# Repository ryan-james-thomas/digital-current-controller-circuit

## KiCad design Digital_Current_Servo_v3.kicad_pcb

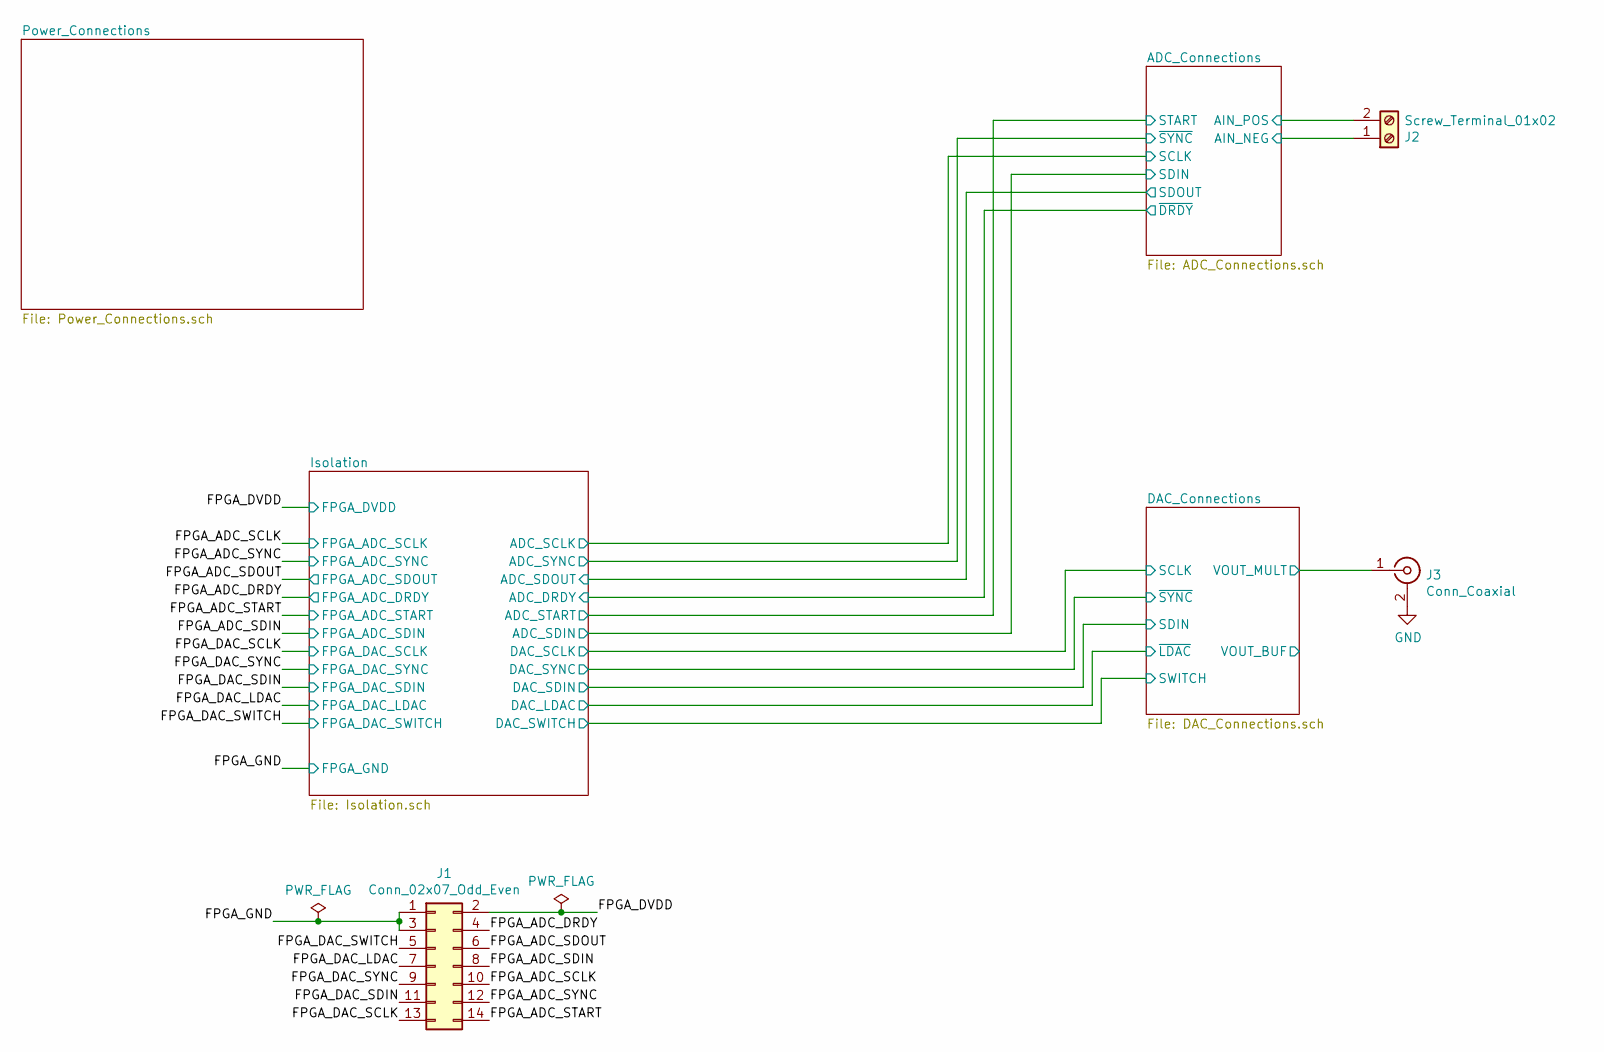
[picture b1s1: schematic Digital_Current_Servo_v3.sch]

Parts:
J1: Conn_02x07_Odd_Even; PinHeader_2x07_P2.54mm_Vertical; Digikey Part Number S2012EC-07-ND
J2: Screw_Terminal_01x02; TerminalBlock_bornier-2_P5.08mm; Digikey Part Number 732-10955-ND
J3: Conn_Coaxial; BNC_Amphenol_B6252HB-NPP3G-50_Horizontal; Digikey Part Number WM5514-ND

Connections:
/ADC_Connections/AIN_NEG: J2.1; also elsewhere on the board
/ADC_Connections/AIN_POS: J2.2; also elsewhere on the board
/DAC_Connections/VOUT_MULT: J3.1 (In); also elsewhere on the board
/FPGA_ADC_DRDY: J1.4; also elsewhere on the board
/FPGA_ADC_SCLK: J1.10; also elsewhere on the board
/FPGA_ADC_SDIN: J1.8; also elsewhere on the board
/FPGA_ADC_SDOUT: J1.6; also elsewhere on the board
/FPGA_ADC_START: J1.14; also elsewhere on the board
/FPGA_ADC_SYNC: J1.12; also elsewhere on the board
/FPGA_DAC_LDAC: J1.7; also elsewhere on the board
/FPGA_DAC_SCLK: J1.13; also elsewhere on the board
/FPGA_DAC_SDIN: J1.11; also elsewhere on the board
/FPGA_DAC_SWITCH: J1.5; also elsewhere on the board
/FPGA_DAC_SYNC: J1.9; also elsewhere on the board
/FPGA_DVDD: J1.2; also elsewhere on the board
/FPGA_GND: J1.1, J1.3; also elsewhere on the board
GND: J3.2 (Ext); also elsewhere on the board

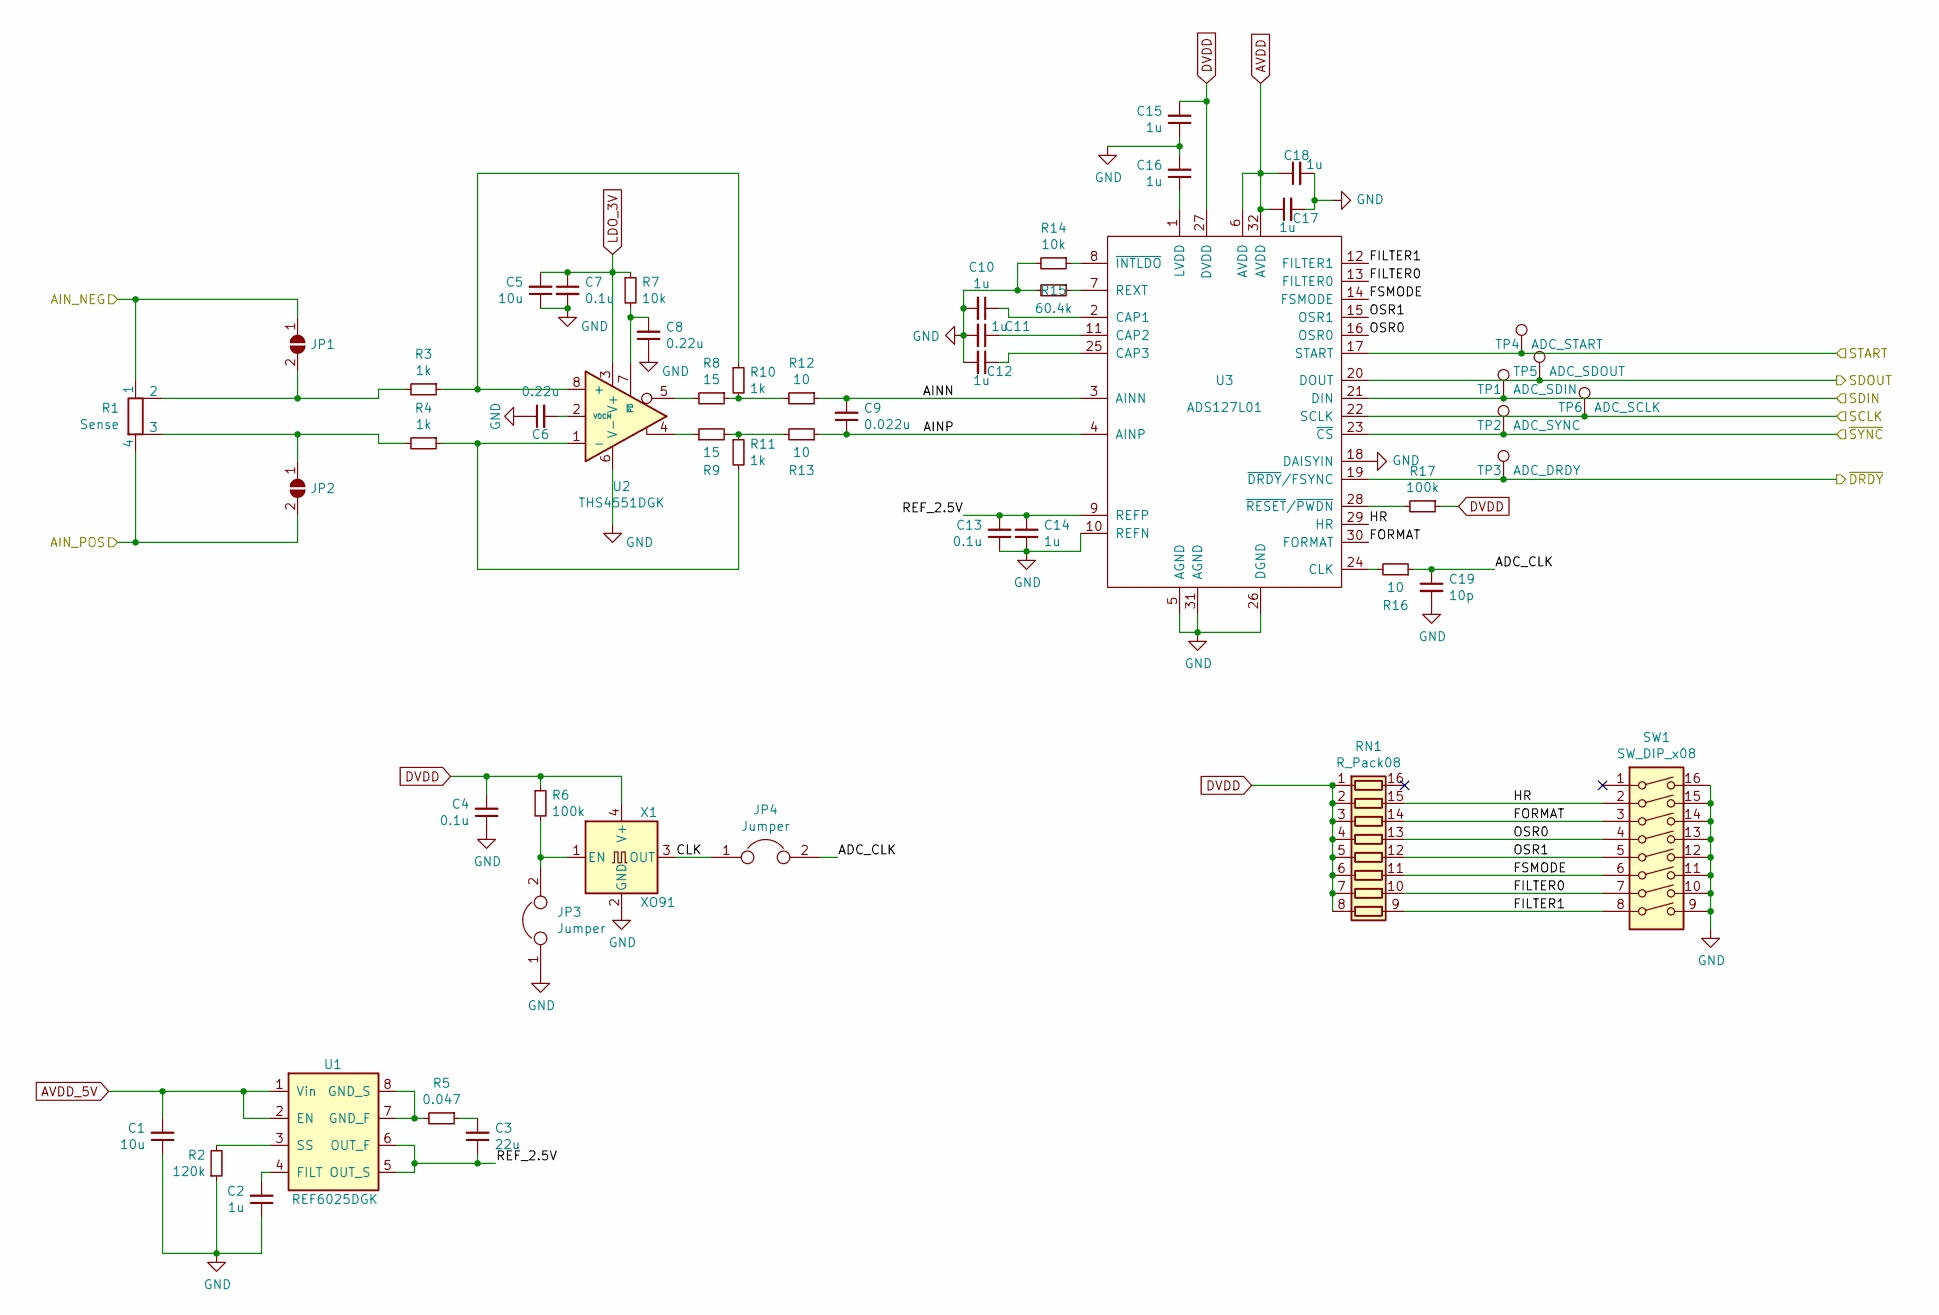
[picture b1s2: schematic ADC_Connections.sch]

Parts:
C1, C5: 10u; C_0805_2012Metric_Pad1.15x1.40mm_HandSolder; Digikey Part Number 1276-1052-1-ND
C2, C10, C11, C12, C14, C15, C16, C17, C18: 1u; C_0805_2012Metric_Pad1.15x1.40mm_HandSolder; Digikey Part Number 1276-6471-1-ND
C3: 22u; C_1206_3216Metric_Pad1.42x1.75mm_HandSolder; Digikey Part Number 1276-1771-1-ND
C4, C7, C13: 0.1u; C_0805_2012Metric_Pad1.15x1.40mm_HandSolder; Digikey Part Number 1276-1003-1-ND
C6, C8: 0.22u; C_0805_2012Metric_Pad1.15x1.40mm_HandSolder; Digikey Part Number 1276-6478-1-ND
C9: 0.022u; C_0805_2012Metric_Pad1.15x1.40mm_HandSolder; Digikey Part Number 399-1163-1-ND
C19: 10p; C_0805_2012Metric_Pad1.15x1.40mm_HandSolder; Digikey Part Number 1276-1109-1-ND
JP1, JP2: SolderJumper_2_Open; SolderJumper-2_P1.3mm_Open_Pad1.0x1.5mm
JP3, JP4: Jumper; PinHeader_1x02_P2.54mm_Vertical; Digikey Part Number S1012EC-02-ND
R1: Sense; TO-220-4_Vertical; Digikey Part Number Y1690-10A-ND
R2: 120k; R_0805_2012Metric_Pad1.15x1.40mm_HandSolder; Digikey Part Number RR12P120KDCT-ND
R3, R4, R10, R11: 1k; R_0805_2012Metric_Pad1.15x1.40mm_HandSolder; Digikey Part Number P1.0KDACT-ND
R5: 0.047; R_0805_2012Metric_Pad1.15x1.40mm_HandSolder; Digikey Part Number 1276-6158-1-ND
R6, R17: 100k; R_0805_2012Metric_Pad1.15x1.40mm_HandSolder; Digikey Part Number 1276-3512-1-ND‎
R7, R14: 10k; R_0805_2012Metric_Pad1.15x1.40mm_HandSolder; Digikey Part Number ‎P10.0KCCT-ND‎
R8, R9: 15; R_0805_2012Metric_Pad1.15x1.40mm_HandSolder; Digikey Part Number YAG4833CT-ND
R12, R13, R16: 10; R_0805_2012Metric_Pad1.15x1.40mm_HandSolder; Digikey Part Number A119971CT-ND
R15: 60.4k; R_0805_2012Metric_Pad1.15x1.40mm_HandSolder; Digikey Part Number RR12P60.4KDCT-ND
RN1: R_Pack08; SOIC-16_W4.9_P1.27; Digikey Part Number 4816P-T01-104LF-ND
SW1: SW_DIP_x08; SOIC-16_W8.6mm_P2.54mm; Digikey Part Number CT2198LPST-ND
TP1: ADC_SDIN; TestPoint_Pad_1.0x1.0mm
TP2: ADC_SYNC; TestPoint_Pad_1.0x1.0mm
TP3: ADC_DRDY; TestPoint_Pad_1.0x1.0mm
TP4: ADC_START; TestPoint_Pad_1.0x1.0mm
TP5: ADC_SDOUT; TestPoint_Pad_1.0x1.0mm
TP6: ADC_SCLK; TestPoint_Pad_1.0x1.0mm
U1: REF6025DGK; VSSOP-8_3.0x3.0mm_P0.65mm; Digikey Part Number 296-51527-1-ND
U2: THS4551DGK; VSSOP-8_3.0x3.0mm_P0.65mm; Digikey Part Number 296-47312-1-ND
U3: ADS127L01; LQFP-32_5x5mm_P0.5mm; Digikey Part Number 296-44344-1-ND
X1: XO91; Oscillator_SMD_Abracon_ASE-4Pin_3.2x2.5mm_HandSoldering; Digikey Part Number 535-11459-1-ND

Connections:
/ADC_Connections/ADC_CLK: C19.1, JP4.2, R16.1
/ADC_Connections/AINN: C9.2, R12.1, U3.3 (AINN)
/ADC_Connections/AINP: C9.1, R13.1, U3.4 (AINP)
/ADC_Connections/AIN_NEG: JP1.1 (A), R1.1; also elsewhere on the board
/ADC_Connections/AIN_POS: JP2.2 (B), R1.4; also elsewhere on the board
/ADC_Connections/CLK: JP4.1, X1.3 (OUT)
/ADC_Connections/FILTER0: RN1.10 (R7.2), SW1.7, U3.13 (FILTER0)
/ADC_Connections/FILTER1: RN1.9 (R8.2), SW1.8, U3.12 (FILTER1)
/ADC_Connections/FORMAT: RN1.14 (R3.2), SW1.3, U3.30 (FORMAT)
/ADC_Connections/FSMODE: RN1.11 (R6.2), SW1.6, U3.14 (FSMODE)
/ADC_Connections/HR: RN1.15 (R2.2), SW1.2, U3.29 (HR)
/ADC_Connections/OSR0: RN1.13 (R4.2), SW1.4, U3.16 (OSR0)
/ADC_Connections/OSR1: RN1.12 (R5.2), SW1.5, U3.15 (OSR1)
/ADC_Connections/REF_2.5V: C3.1, C13.2, C14.2, U1.5 (OUT_S), U1.6 (OUT_F), U3.9 (REFP)
/Isolation/ADC_DRDY: TP3.1, U3.19 (~DRDY~/FSYNC); also elsewhere on the board
/Isolation/ADC_SCLK: TP6.1, U3.22 (SCLK); also elsewhere on the board
/Isolation/ADC_SDIN: TP1.1, U3.21 (DIN); also elsewhere on the board
/Isolation/ADC_SDOUT: TP5.1, U3.20 (DOUT); also elsewhere on the board
/Isolation/ADC_START: TP4.1, U3.17 (START); also elsewhere on the board
/Isolation/ADC_SYNC: TP2.1, U3.23 (~CS); also elsewhere on the board
AVDD: C17.1, C18.1, U3.6 (AVDD), U3.32 (AVDD); also elsewhere on the board
AVDD_5V: C1.2, U1.1 (Vin), U1.2 (EN); also elsewhere on the board
DVDD: C4.2, C15.2, R6.1, R17.1, RN1.1 (R1.1), RN1.2 (R2.1), RN1.3 (R3.1), RN1.4 (R4.1), RN1.5 (R5.1), RN1.6 (R6.1), RN1.7 (R7.1), RN1.8 (R8.1), U3.27 (DVDD), X1.4 (V+); also elsewhere on the board
GND: C1.1, C2.1, C4.1, C5.1, C6.1, C7.2, C8.1, C10.2, C11.2, C12.2, C13.1, C14.1, C15.1, C16.2, C17.2, C18.2, C19.2, JP3.1, R2.1, R14.2, R15.2, SW1.9, SW1.10, SW1.11, SW1.12, SW1.13, SW1.14, SW1.15, SW1.16, U2.6 (V-), U3.5 (AGND), U3.10 (REFN), U3.18 (DAISYIN), U3.26 (DGND), U3.31 (AGND), X1.2 (GND); also elsewhere on the board
LDO_3V: C5.2, C7.1, R7.1, U2.3 (V+); also elsewhere on the board
unnamed: C2.2, U1.4 (FILT)
unnamed: C3.2, R5.1
unnamed: C6.2, U2.2 (VOCM)
unnamed: C8.2, R7.2, U2.7 (~PD)
unnamed: C10.1, U3.2 (CAP1)
unnamed: C11.1, U3.11 (CAP2)
unnamed: C12.1, U3.25 (CAP3)
unnamed: C16.1, U3.1 (LVDD)
unnamed: JP1.2 (B), R1.2, R3.2
unnamed: JP2.1 (A), R1.3, R4.2
unnamed: JP3.2, R6.2, X1.1 (EN)
unnamed: R2.2, U1.3 (SS)
unnamed: R5.2, U1.7 (GND_F), U1.8 (GND_S)
unnamed: R8.2, U2.5
unnamed: R9.1, U2.4
unnamed: R3.1, R10.1, U2.8 (+)
unnamed: R8.1, R10.2, R12.2
unnamed: R9.2, R11.1, R13.2
unnamed: R4.1, R11.2, U2.1 (-)
unnamed: R14.1, U3.8 (~INTLDO)
unnamed: R15.1, U3.7 (REXT)
unnamed: R16.2, U3.24 (CLK)
unnamed: R17.2, U3.28 (~RESET~/~PWDN)

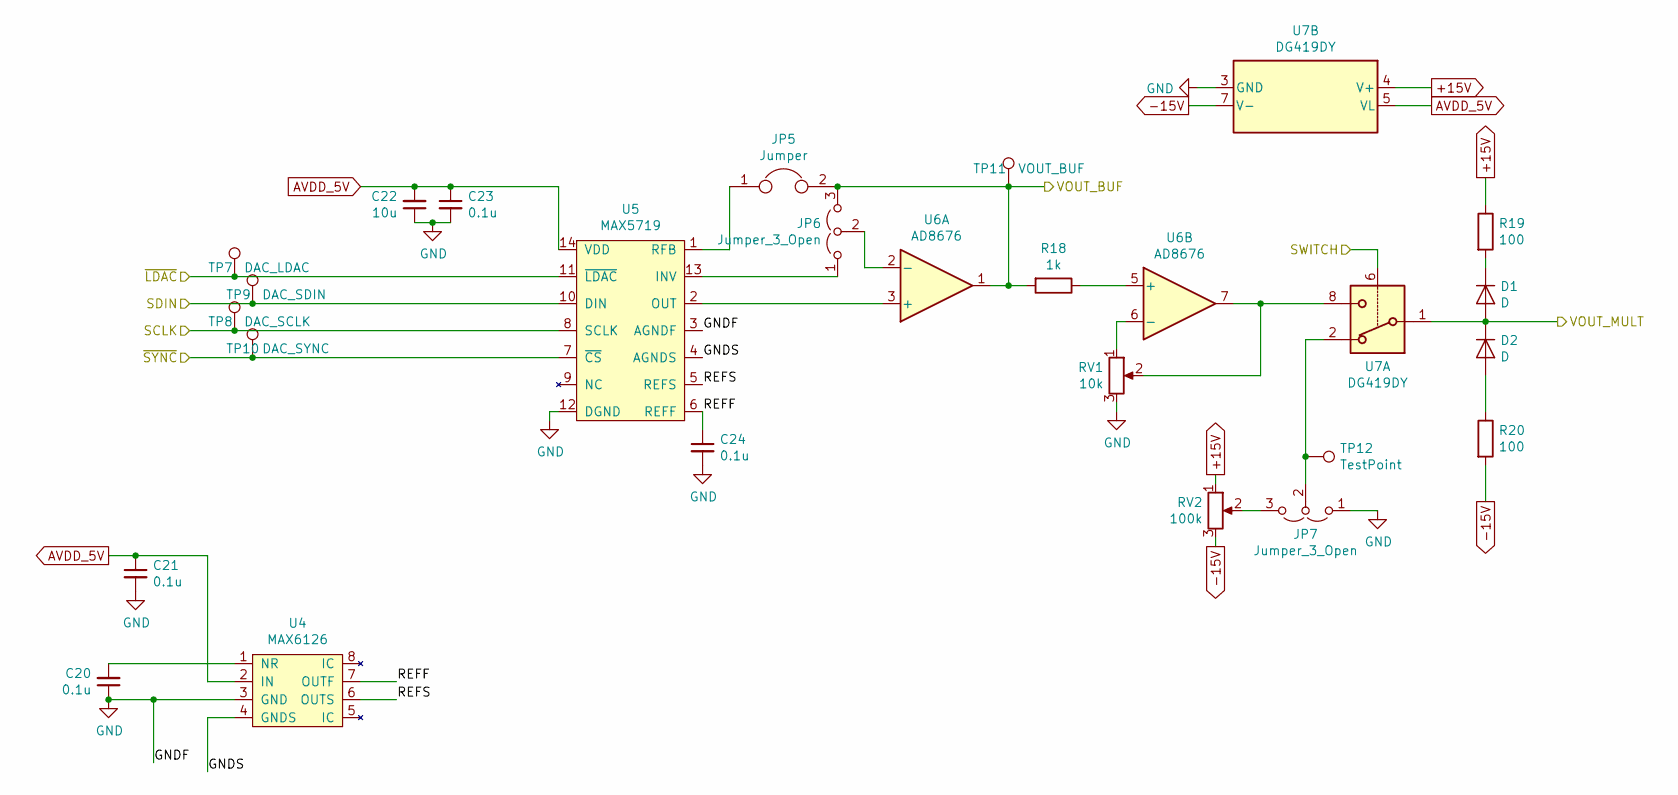
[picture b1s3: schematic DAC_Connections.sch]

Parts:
C20, C21, C23, C24: 0.1u; C_0805_2012Metric_Pad1.15x1.40mm_HandSolder; Digikey Part Number 1276-1003-1-ND
C22: 10u; C_0805_2012Metric_Pad1.15x1.40mm_HandSolder; Digikey Part Number 1276-1052-1-ND
D1, D2: D; D_DO-41_SOD81_P7.62mm_Horizontal; Digikey Part Number 1N4007-TPMSCT-ND
JP5: Jumper; PinHeader_1x02_P2.54mm_Vertical; Digikey Part Number S1012EC-02-ND
JP6, JP7: Jumper_3_Open; PinHeader_1x03_P2.54mm_Vertical; Digikey Part Number S1012EC-03-ND
R18: 1k; R_0805_2012Metric_Pad1.15x1.40mm_HandSolder; Digikey Part Number P1.0KDACT-ND
R19, R20: 100; R_Axial_DIN0207_L6.3mm_D2.5mm_P7.62mm_Horizontal; Digikey Part Number CF14JT100RCT-ND
RV1: 10k; Potentiometer_Bourns_3296W_Vertical; Digikey Part Number 490-2875-ND
RV2: 100k; Potentiometer_Bourns_3296W_Vertical; Digikey Part Number 490-2876-ND
TP7: DAC_LDAC; TestPoint_Pad_1.0x1.0mm
TP8: DAC_SCLK; TestPoint_Pad_1.0x1.0mm
TP9: DAC_SDIN; TestPoint_Pad_1.0x1.0mm
TP10: DAC_SYNC; TestPoint_Pad_1.0x1.0mm
TP11: VOUT_BUF; TestPoint_Pad_1.0x1.0mm
TP12: TestPoint; TestPoint_Pad_1.0x1.0mm
U4: MAX6126; SOIC-8_3.9x4.9mm_P1.27mm; Digikey Part Number MAX6126BASA41+-ND
U5: MAX5719; SOIC-14_3.9x8.7mm_P1.27mm; Digikey Part Number MAX5719GSD+-ND
U6: AD8676; SOIC-8_3.9x4.9mm_P1.27mm; Digikey Part Number AD8676ARZ-ND
U7: DG419DY; SOIC-8_3.9x4.9mm_P1.27mm; Digikey Part Number DG419DY-T1-E3CT-ND

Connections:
+15V: R19.1, RV2.1, U7.4 (V+); also elsewhere on the board
-15V: R20.2, RV2.3, U7.7 (V-); also elsewhere on the board
/DAC_Connections/GNDS: U4.4 (GNDS), U5.4 (AGNDS)
/DAC_Connections/REFF: C24.1, U4.7 (OUTF), U5.6 (REFF)
/DAC_Connections/REFS: U4.6 (OUTS), U5.5 (REFS)
/DAC_Connections/VOUT_BUF: JP5.2, JP6.3 (B), R18.2, TP11.1, U6.1
/DAC_Connections/VOUT_MULT: D1.2 (A), D2.1 (K), U7.1; also elsewhere on the board
/Isolation/DAC_LDAC: TP7.1, U5.11 (~LDAC); also elsewhere on the board
/Isolation/DAC_SCLK: TP8.1, U5.8 (SCLK); also elsewhere on the board
/Isolation/DAC_SDIN: TP9.1, U5.10 (DIN); also elsewhere on the board
/Isolation/DAC_SWITCH: U7.6; also elsewhere on the board
/Isolation/DAC_SYNC: TP10.1, U5.7 (~CS); also elsewhere on the board
AVDD_5V: C21.1, C22.2, C23.1, U4.2 (IN), U5.14 (VDD), U7.5 (VL); also elsewhere on the board
GND: C20.1, C21.2, C22.1, C23.2, C24.2, JP7.1 (A), RV1.3, U4.3 (GND), U5.3 (AGNDF), U5.12 (DGND), U7.3 (GND); also elsewhere on the board
unnamed: C20.2, U4.1 (NR)
unnamed: D1.1 (K), R19.2
unnamed: D2.2 (A), R20.1
unnamed: JP5.1, U5.1 (RFB)
unnamed: JP6.1 (A), U5.13 (INV)
unnamed: JP6.2 (C), U6.2 (-)
unnamed: JP7.2 (C), TP12.1, U7.2
unnamed: JP7.3 (B), RV2.2
unnamed: R18.1, U6.5 (+)
unnamed: RV1.1, U6.6 (-)
unnamed: RV1.2, U6.7, U7.8
unnamed: U5.2 (OUT), U6.3 (+)

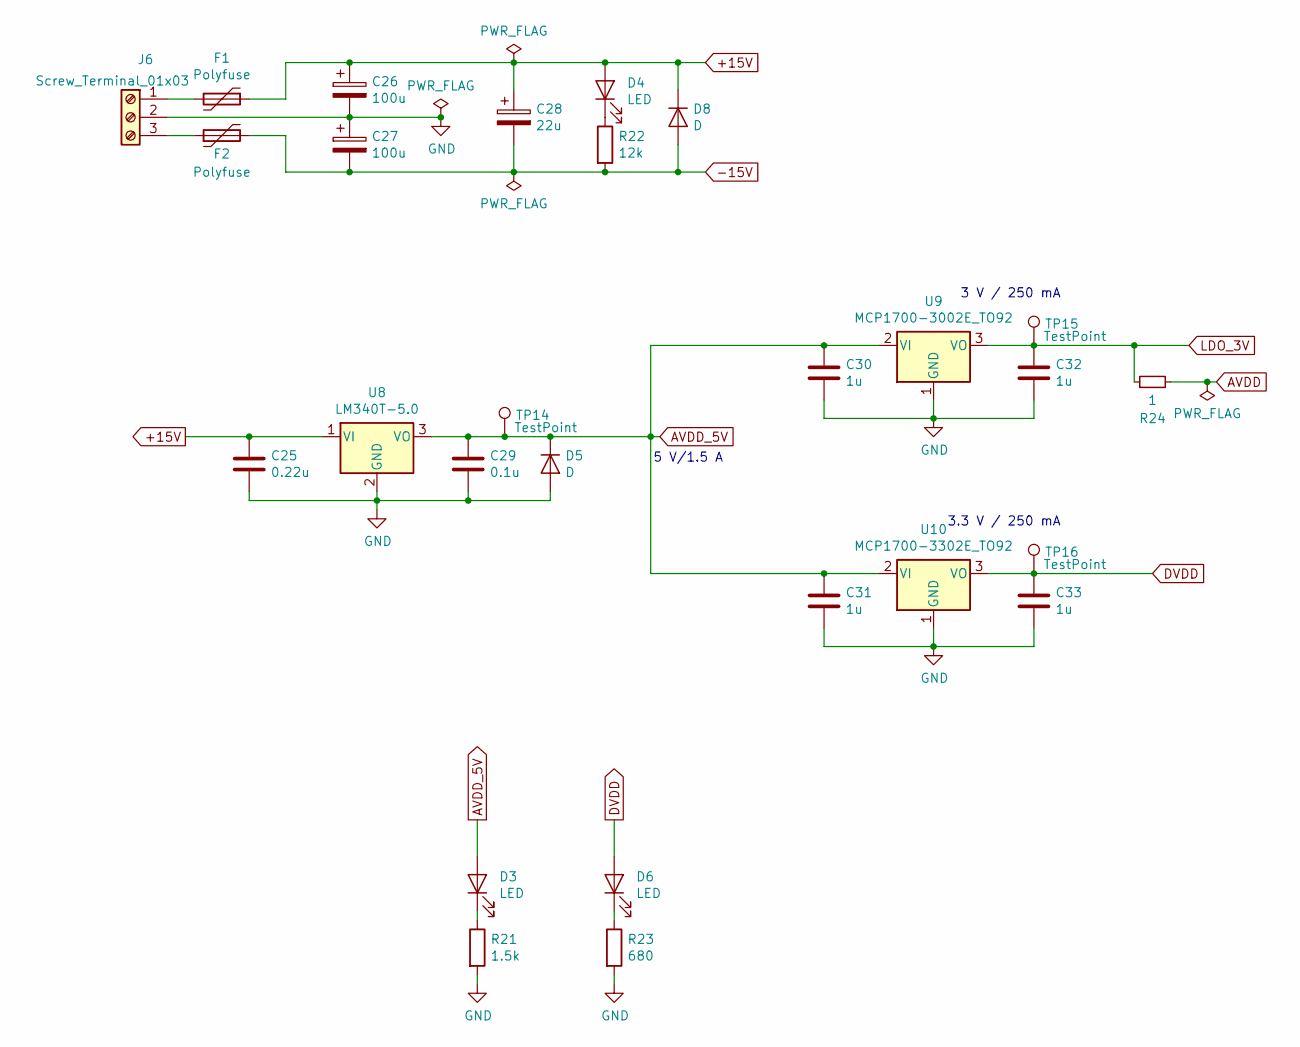
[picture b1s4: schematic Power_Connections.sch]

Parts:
C25: 0.22u; C_0805_2012Metric_Pad1.15x1.40mm_HandSolder; Digikey Part Number 1276-6478-1-ND
C26, C27: 100u; CP_Radial_D8.0mm_P3.50mm; Digikey Part Number 732-8666-1-ND
C28: 22u; CP_Radial_D5.0mm_P2.00mm; Digikey Part Number 732-8662-1-ND
C29: 0.1u; C_0805_2012Metric_Pad1.15x1.40mm_HandSolder; Digikey Part Number 1276-1003-1-ND
C30, C31, C32, C33: 1u; C_0805_2012Metric_Pad1.15x1.40mm_HandSolder; Digikey Part Number 1276-6471-1-ND
D3, D6: LED; LED_0805_2012Metric_Pad1.15x1.40mm_HandSolder; Digikey Part Number 754-2043-1-ND
D4: LED; LED_D5.0mm; Digikey Part Number 732-5020-ND
D5, D8: D; D_DO-41_SOD81_P7.62mm_Horizontal; Digikey Part Number 1N4007-TPMSCT-ND
F1, F2: Polyfuse; Fuse_1206_3216Metric_Pad1.42x1.75mm_HandSolder; Digikey Part Number 507-1803-1-ND
J6: Screw_Terminal_01x03; TerminalBlock_bornier-3_P5.08mm; Digikey Part Number 732-10956-ND
R21: 1.5k; R_0805_2012Metric_Pad1.15x1.40mm_HandSolder; Digikey Part Number RHM1.5KKCT-ND
R22: 12k; R_0805_2012Metric_Pad1.15x1.40mm_HandSolder; Digikey Part Number A126337CT-ND
R23: 680; R_0805_2012Metric_Pad1.15x1.40mm_HandSolder; Digikey Part Number A129747CT-ND
R24: 1; R_0805_2012Metric_Pad1.15x1.40mm_HandSolder; Digikey Part Number CSR0805FK1R00CT-ND
TP14, TP15, TP16: TestPoint; TestPoint_Pad_1.0x1.0mm
U8: LM340T-5.0; TO-220-3_Vertical; Digikey Part Number LM340T-5.0/NOPB-ND
U9: MCP1700-3002E_TO92; TO-92_Inline; Digikey Part Number MCP1700-3002E/TO-ND
U10: MCP1700-3302E_TO92; TO-92_Inline; Digikey Part Number MCP1700-3302E/TO-ND

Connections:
+15V: C25.1, C26.1, C28.1, D4.2 (A), D8.1 (K), F1.1, U8.1 (VI); also elsewhere on the board
-15V: C27.2, C28.2, D8.2 (A), F2.2, R22.2; also elsewhere on the board
AVDD: R24.2; also elsewhere on the board
AVDD_5V: C29.1, C30.1, C31.1, D3.2 (A), D5.1 (K), TP14.1, U8.3 (VO), U9.2 (VI), U10.2 (VI); also elsewhere on the board
DVDD: C33.1, D6.2 (A), TP16.1, U10.3 (VO); also elsewhere on the board
GND: C25.2, C26.2, C27.1, C29.2, C30.2, C31.2, C32.2, C33.2, D5.2 (A), J6.2, R21.2, R23.2, U8.2 (GND), U9.1 (GND), U10.1 (GND); also elsewhere on the board
LDO_3V: C32.1, R24.1, TP15.1, U9.3 (VO); also elsewhere on the board
unnamed: D3.1 (K), R21.1
unnamed: D4.1 (K), R22.1
unnamed: D6.1 (K), R23.1
unnamed: F1.2, J6.1
unnamed: F2.1, J6.3

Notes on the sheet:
5 V/1.5 A
3 V / 250 mA
3.3 V / 250 mA

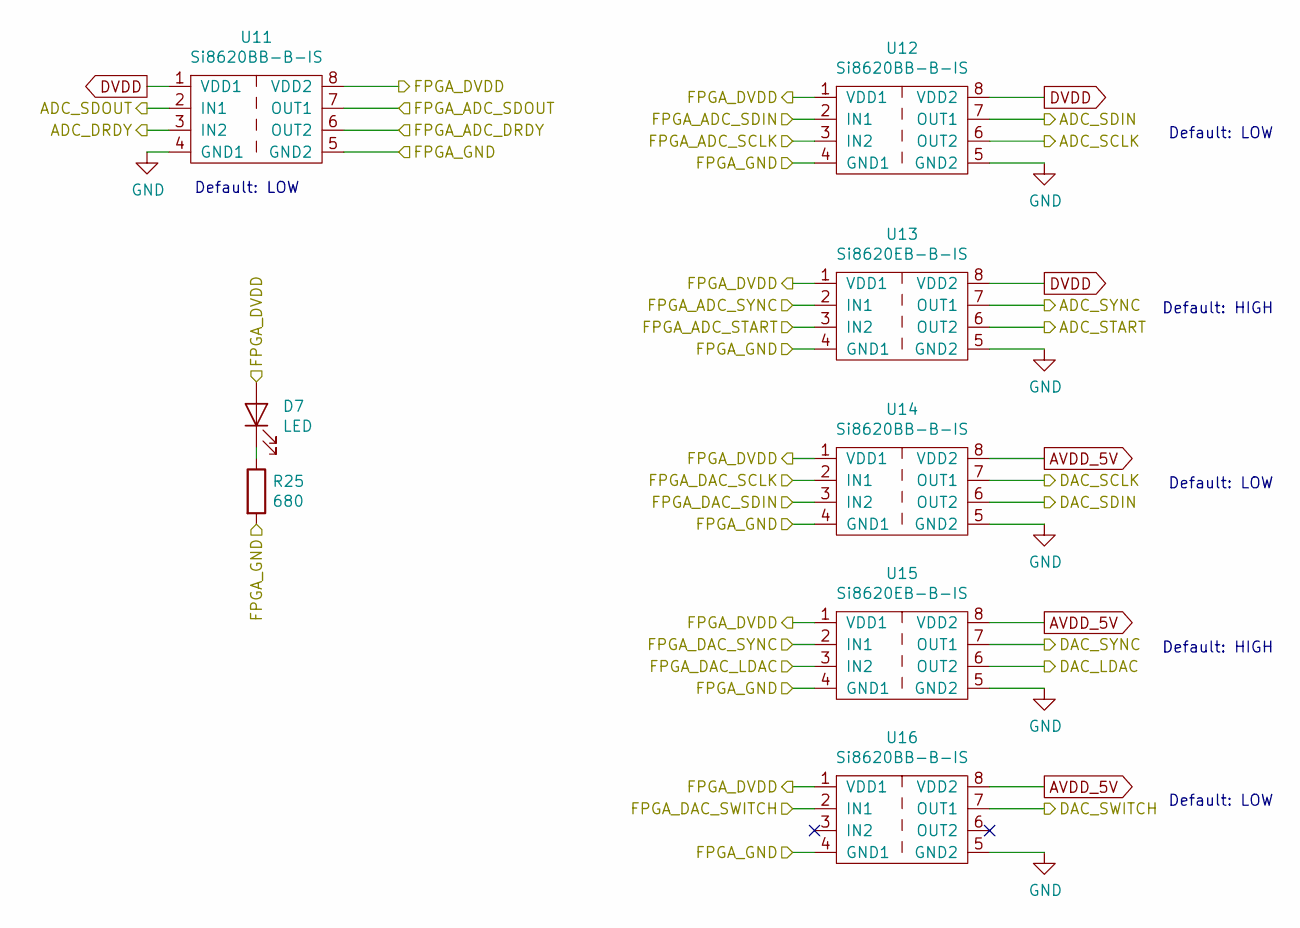
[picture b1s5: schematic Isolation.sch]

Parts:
D7: LED; LED_0805_2012Metric_Pad1.15x1.40mm_HandSolder; Digikey Part Number 754-2043-1-ND
R25: 680; R_0805_2012Metric_Pad1.15x1.40mm_HandSolder; Digikey Part Number A129747CT-ND
U11, U12, U14, U16: Si8620BB-B-IS; SOIC-8_3.9x4.9mm_P1.27mm; Digikey Part Number 336-4209-1-ND
U13, U15: Si8620EB-B-IS; SOIC-8_3.9x4.9mm_P1.27mm; Digikey Part Number SI8620EB-B-IS-ND

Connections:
/FPGA_ADC_DRDY: U11.6 (OUT2); also elsewhere on the board
/FPGA_ADC_SCLK: U12.3 (IN2); also elsewhere on the board
/FPGA_ADC_SDIN: U12.2 (IN1); also elsewhere on the board
/FPGA_ADC_SDOUT: U11.7 (OUT1); also elsewhere on the board
/FPGA_ADC_START: U13.3 (IN2); also elsewhere on the board
/FPGA_ADC_SYNC: U13.2 (IN1); also elsewhere on the board
/FPGA_DAC_LDAC: U15.3 (IN2); also elsewhere on the board
/FPGA_DAC_SCLK: U14.2 (IN1); also elsewhere on the board
/FPGA_DAC_SDIN: U14.3 (IN2); also elsewhere on the board
/FPGA_DAC_SWITCH: U16.2 (IN1); also elsewhere on the board
/FPGA_DAC_SYNC: U15.2 (IN1); also elsewhere on the board
/FPGA_DVDD: D7.2 (A), U11.8 (VDD2), U12.1 (VDD1), U13.1 (VDD1), U14.1 (VDD1), U15.1 (VDD1), U16.1 (VDD1); also elsewhere on the board
/FPGA_GND: R25.2, U11.5 (GND2), U12.4 (GND1), U13.4 (GND1), U14.4 (GND1), U15.4 (GND1), U16.4 (GND1); also elsewhere on the board
/Isolation/ADC_DRDY: U11.3 (IN2); also elsewhere on the board
/Isolation/ADC_SCLK: U12.6 (OUT2); also elsewhere on the board
/Isolation/ADC_SDIN: U12.7 (OUT1); also elsewhere on the board
/Isolation/ADC_SDOUT: U11.2 (IN1); also elsewhere on the board
/Isolation/ADC_START: U13.6 (OUT2); also elsewhere on the board
/Isolation/ADC_SYNC: U13.7 (OUT1); also elsewhere on the board
/Isolation/DAC_LDAC: U15.6 (OUT2); also elsewhere on the board
/Isolation/DAC_SCLK: U14.7 (OUT1); also elsewhere on the board
/Isolation/DAC_SDIN: U14.6 (OUT2); also elsewhere on the board
/Isolation/DAC_SWITCH: U16.7 (OUT1); also elsewhere on the board
/Isolation/DAC_SYNC: U15.7 (OUT1); also elsewhere on the board
AVDD_5V: U14.8 (VDD2), U15.8 (VDD2), U16.8 (VDD2); also elsewhere on the board
DVDD: U11.1 (VDD1), U12.8 (VDD2), U13.8 (VDD2); also elsewhere on the board
GND: U11.4 (GND1), U12.5 (GND2), U13.5 (GND2), U14.5 (GND2), U15.5 (GND2), U16.5 (GND2); also elsewhere on the board
unnamed: D7.1 (K), R25.1

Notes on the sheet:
Default: LOW
Default: HIGH

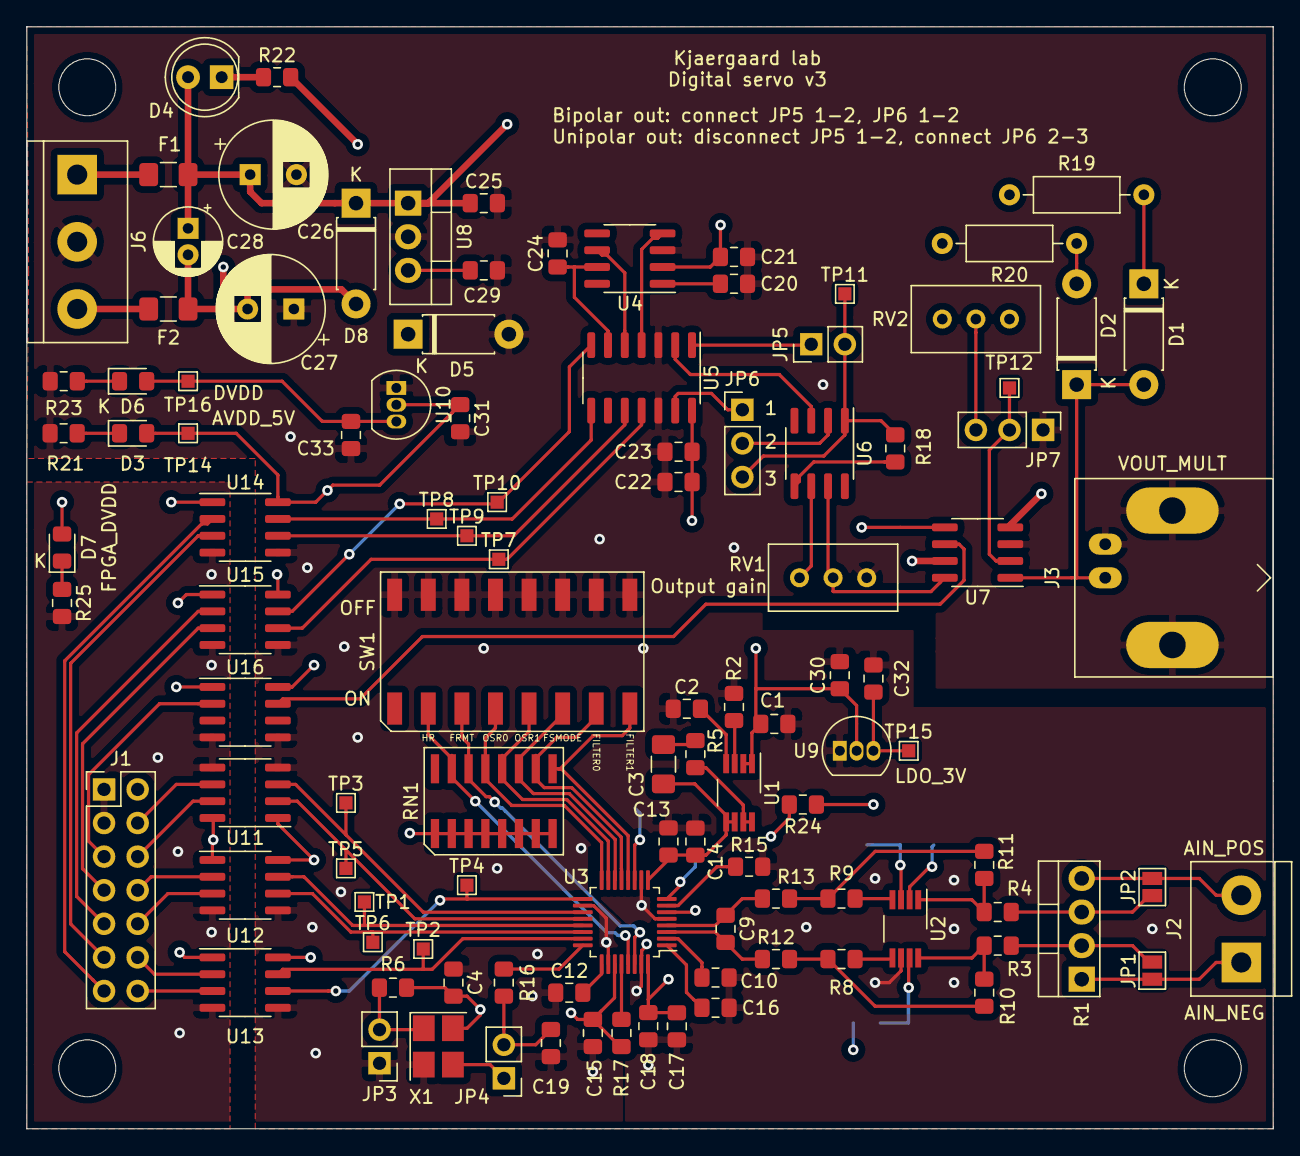
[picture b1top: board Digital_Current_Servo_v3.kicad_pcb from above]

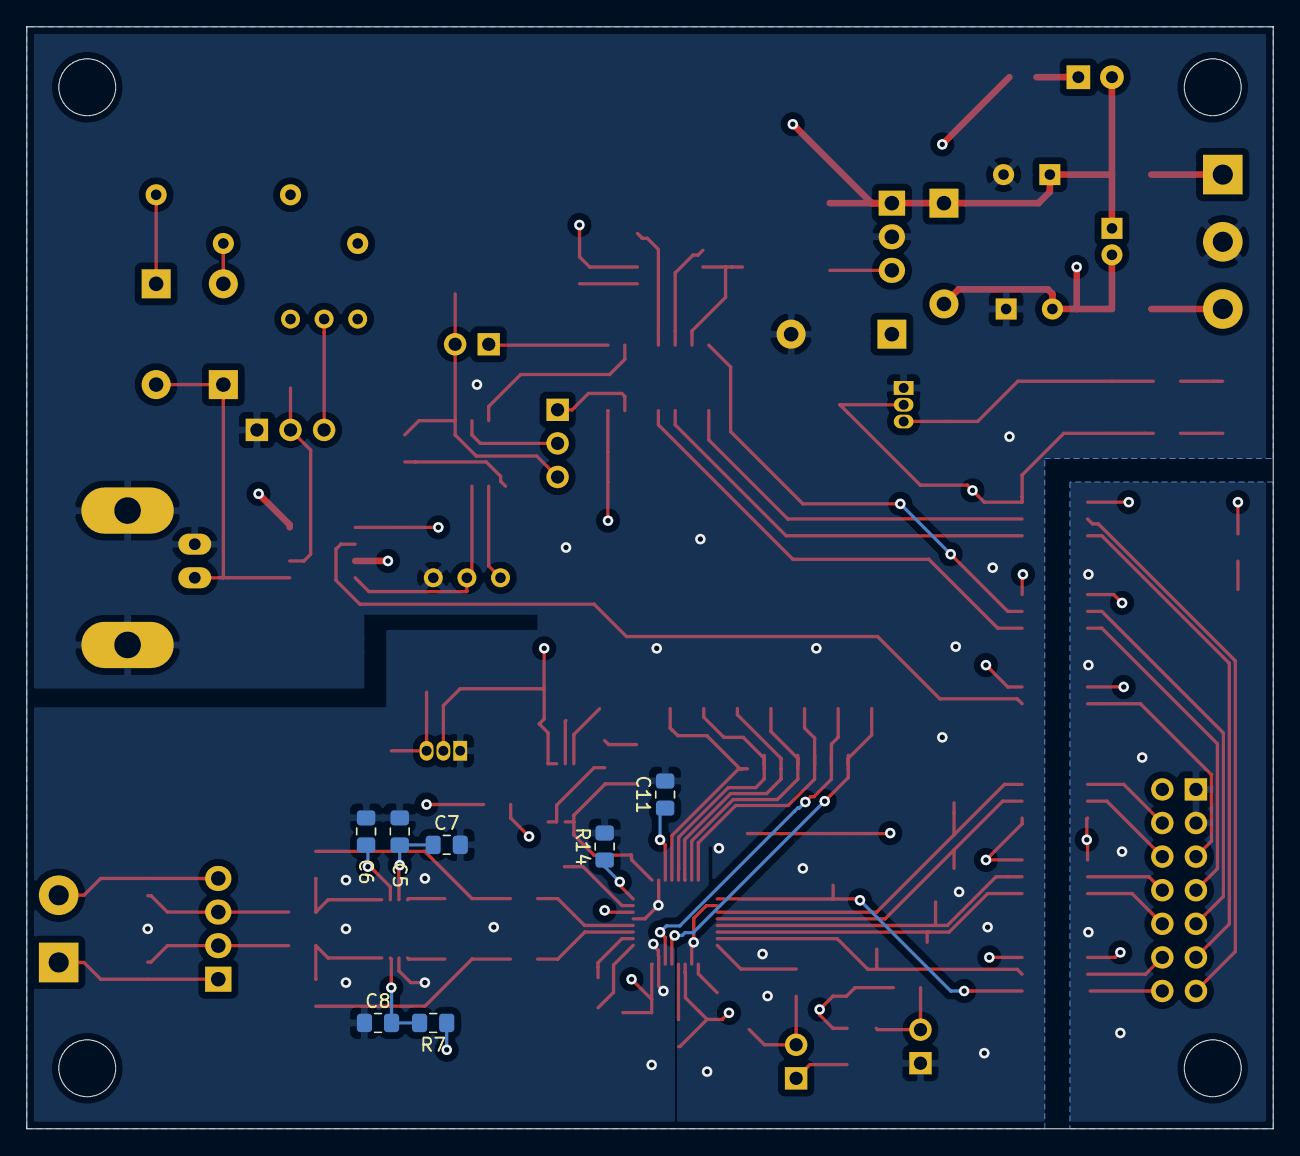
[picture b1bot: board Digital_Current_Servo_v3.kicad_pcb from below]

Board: 4 copper layers, 94.2 x 83.3 mm, 115 parts (7 on the bottom side), 91 nets.

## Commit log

2023-01-15 Initial commit. Files for KiCAD 5.1.4
